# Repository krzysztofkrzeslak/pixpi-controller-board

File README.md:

### PiXPi controller board source

This are sources for PiXPi controller board

Morea bout project on: https://hackaday.io/project/166730-pixpi-dslr-camera-controller

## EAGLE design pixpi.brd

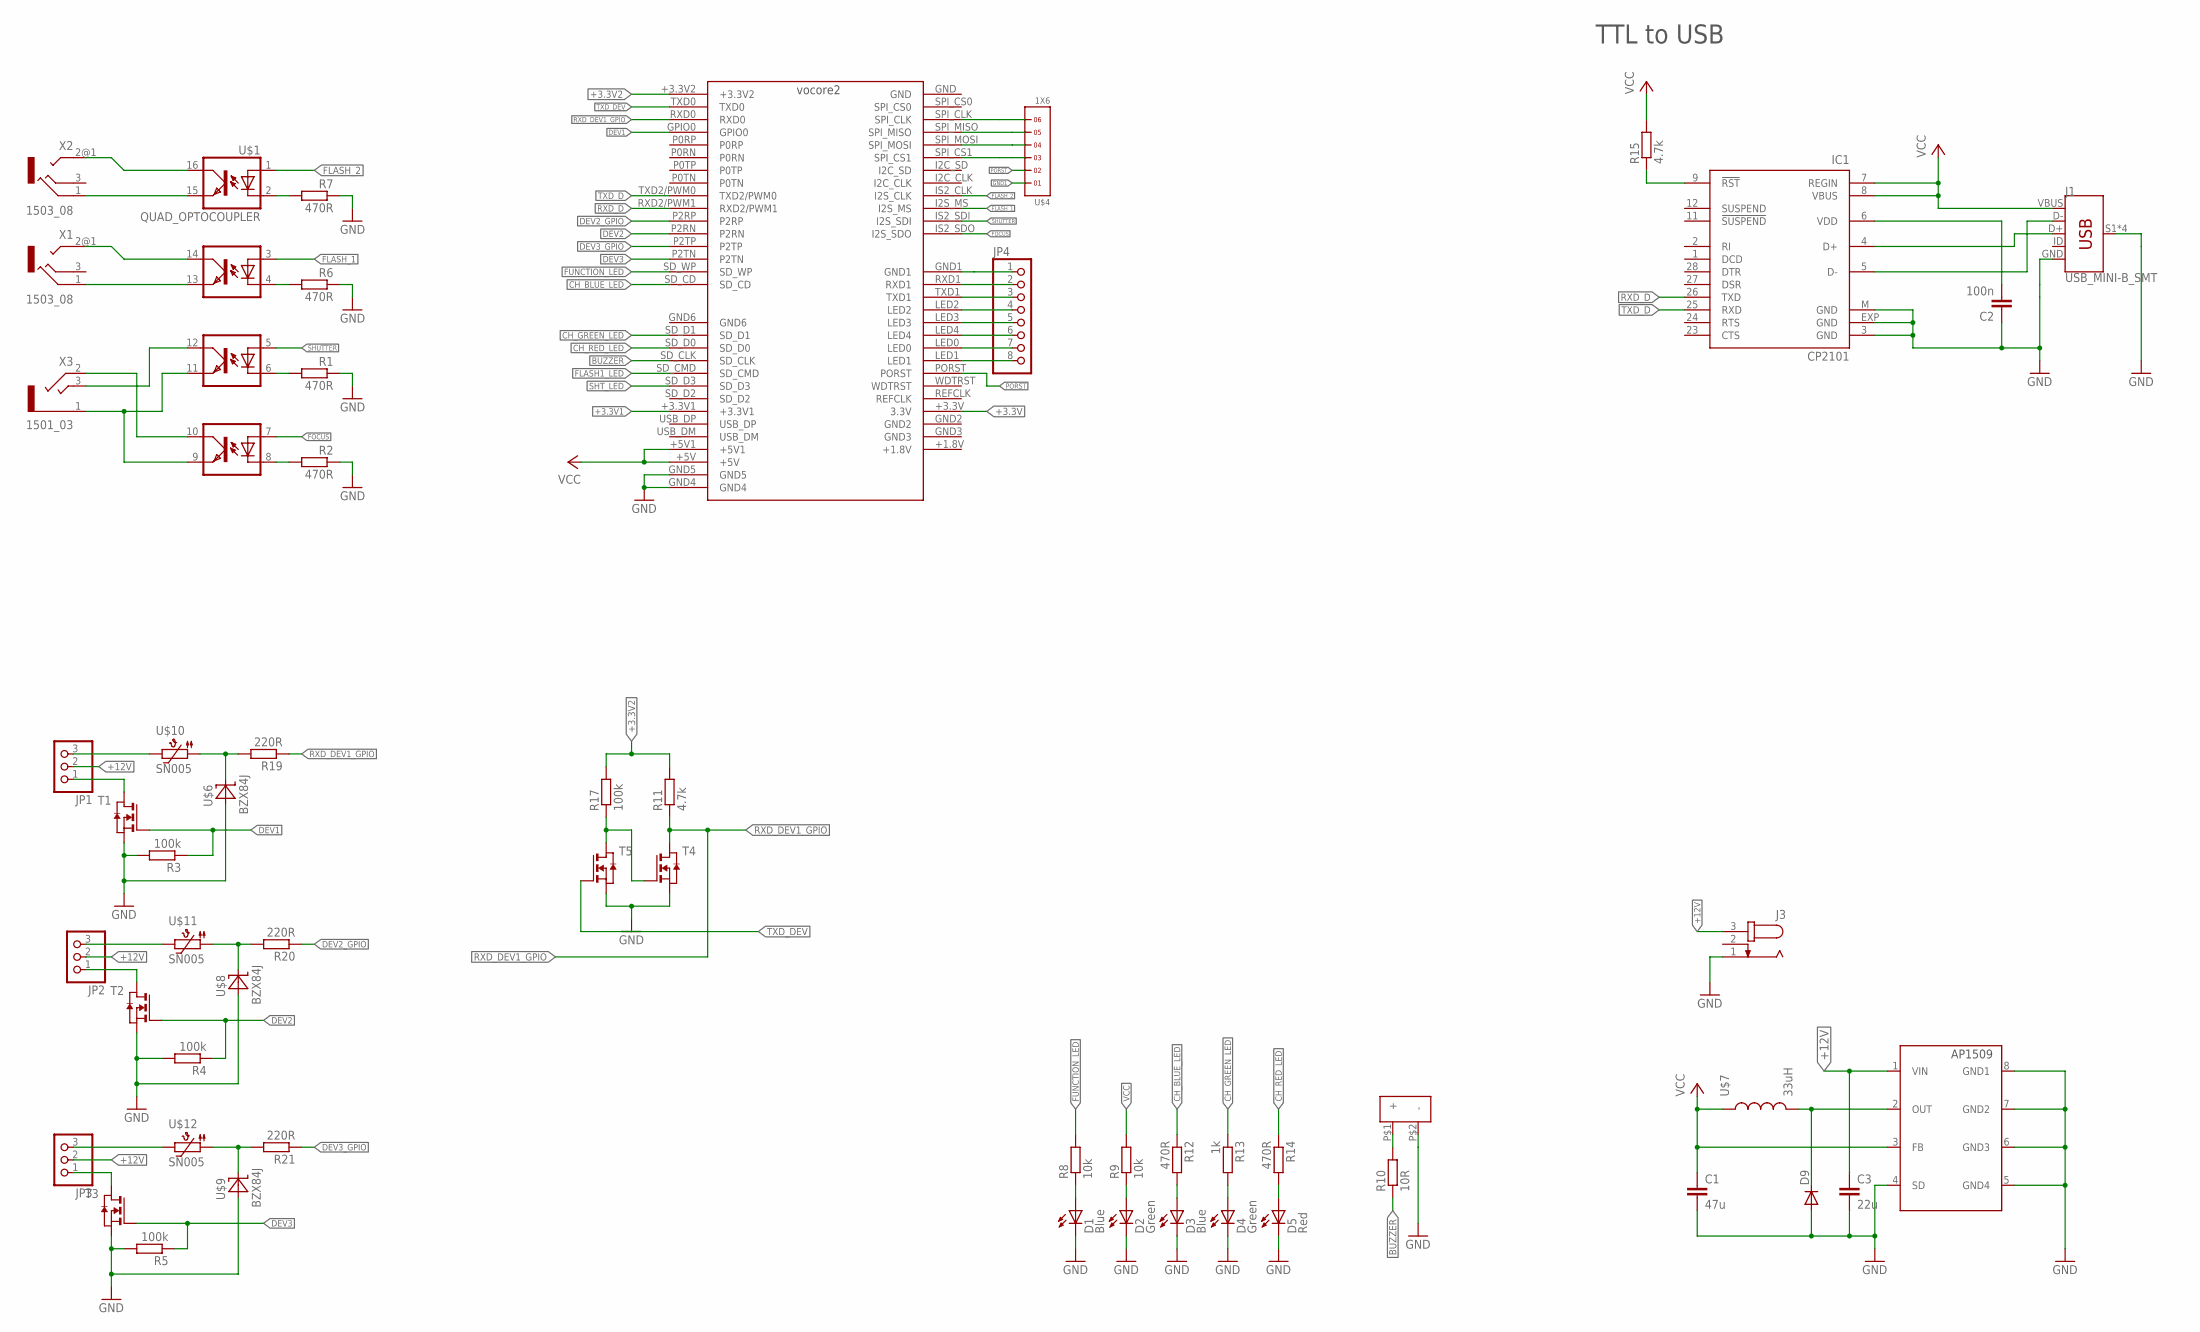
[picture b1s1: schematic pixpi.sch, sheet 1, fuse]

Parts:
C1: 47u; C1210
C2: 100n; C0805
C3: 22u; C1210
D1: Blue; CHIPLED_0603
D2: Green; CHIPLED_0603
D3: Blue; CHIPLED_1206
D4: Green; CHIPLED_1206
D5: Red; CHIPLED_1206
D9: DIODE-SOD323-W; SOD323-W
IC1: CP2101; MLP28
J1: USB_MINI-B_SMT; USB-MINIB
J3: JACK-PLUG0; SPC4077
JP1, JP2, JP3: PINHD-1X3/90; 1X03/90
JP4: PINHD-1X8; 1X08
R1, R2, R6, R7, R12, R14: 470R; R0805
R3, R4, R5, R17: 100k; R0805
R8, R9: 10k; R0805
R10: 10R; R0805
R11, R15: 4.7k; R0805
R13: 1k; R0805
R19, R20, R21: 220R; R0805
T1, T2, T3, T4, T5: NMOSSOT23; SOT-23
U$1: QUAD_OPTOCOUPLER; SO16
U$2: VOCORE2
U$3: LD-BZEG-0905
U$4: 1X6
U$5: AP1509; SOP08
U$6, U$8, U$9: BZX84J; SOD323_ST
U$7: 33uH; DJNR6028
U$10, U$11, U$12: SN005; R1206
X1, X2: 1503_08
X3: 1501_03

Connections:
+3.3V: U$2.+3.3V (3.3V)
+3.3V1: U$2.+3.3V1
+3.3V2: R11.2, R17.2, U$2.+3.3V2
+12V: C3.1, J3.3, JP1.2, JP2.2, JP3.2, U$5.1 (VIN)
BUZZER: R10.1, U$2.SD_CLK
CH_BLUE_LED: R12.1, U$2.SD_CD
CH_GREEN_LED: R13.1, U$2.SD_D1
CH_RED_LED: R14.1, U$2.SD_D0
DEV1: R3.1, T1.3 (G), U$2.GPIO0
DEV2: R4.1, T2.3 (G), U$2.P2RN
DEV2_GPIO: R20.1, U$2.P2RP
DEV3: R5.1, T3.3 (G), U$2.P2TN
DEV3_GPIO: R21.1, U$2.P2TP
FLASH1_LED: U$2.SD_CMD
FLASH_1: U$1.3 (A1), U$2.I2S_MS
FLASH_2: U$1.1 (A), U$2.IS2_CLK (I2S_CLK)
FOCUS: U$1.7 (A3), U$2.IS2_SDO (I2S_SDO)
FUNCTION_LED: R8.2, U$2.SD_WP
GND: C1.2, C2.1, C3.2, D1.C, D2.C, D3.C, D4.C, D5.C, D9.A, IC1.3 (GND), IC1.EXP (GND), IC1.M (GND), J1.GND, J1.S1 (SHIELD), J1.S2 (SHIELD), J1.S3 (SHIELD), J1.S4 (SHIELD), J3.1, R1.1, R2.1, R3.2, R4.2, R5.2, R6.1, R7.1, T1.2 (S), T2.2 (S), T3.2 (S), T4.2 (S), T5.2 (S), U$2.GND4, U$2.GND5, U$3.P$2 (-), U$5.4 (SD), U$5.5 (GND4), U$5.6 (GND3), U$5.7 (GND2), U$5.8 (GND1), U$6.A, U$8.A, U$9.A
GND1: JP4.1, U$2.GND1, U$4.1
unnamed: JP2.1, T2.1 (D)
unnamed: R19.2, U$6.C, U$10.1
unnamed: D9.C, U$5.2 (OUT), U$7.P$4 (2)
unnamed: U$1.13 (EMIT1), X1.1
unnamed: U$1.10 (COL3), X3.2
unnamed: JP1.3, U$10.2
unnamed: R6.2, U$1.4 (C1)
unnamed: JP3.1, T3.1 (D)
unnamed: R21.2, U$9.C, U$12.1
unnamed: U$1.12 (COL2), X3.3
unnamed: U$1.9 (EMIT3), U$1.11 (EMIT2), X3.1
unnamed: R1.2, U$1.6 (C2)
unnamed: R10.2, U$3.P$1 (+)
unnamed: R2.2, U$1.8 (C3)
unnamed: JP2.3, U$11.2
unnamed: U$1.14 (COL1), X1.2@1 (2)
unnamed: JP3.3, U$12.2
unnamed: D2.A, R9.1
unnamed: D1.A, R8.1
unnamed: R20.2, U$8.C, U$11.1
unnamed: JP1.1, T1.1 (D)
unnamed: IC1.9 (!RST), R15.1
unnamed: U$2.SPI_CS1, U$4.3
unnamed: IC1.5 (D-), J1.D-
unnamed: IC1.4 (D+), J1.D+
unnamed: C2.2, IC1.6 (VDD)
unnamed: U$2.SPI_MOSI, U$4.4
unnamed: U$2.SPI_MISO, U$4.5
unnamed: U$2.SPI_CLK, U$4.6
unnamed: R17.1, T4.3 (G), T5.1 (D)
unnamed: D3.A, R12.2
unnamed: D4.A, R13.2
unnamed: U$1.15 (EMIT), X2.1
unnamed: U$1.16 (COL), X2.2@1 (2)
unnamed: D5.A, R14.2
unnamed: R7.2, U$1.2 (C)
unnamed: JP4.2, U$2.RXD1
unnamed: JP4.3, U$2.TXD1
unnamed: JP4.4, U$2.LED2
unnamed: JP4.5, U$2.LED3
unnamed: JP4.6, U$2.LED4
unnamed: JP4.7, U$2.LED0
unnamed: JP4.8, U$2.LED1
PORST: U$2.PORST, U$4.2
RXD_D: IC1.26 (TXD), U$2.RXD2/PWM1
RXD_DEV1_GPIO: R11.1, R19.1, T4.1 (D), U$2.RXD0
SHT_LED: U$2.SD_D3
SHUTTER: U$1.5 (A2), U$2.IS2_SDI (I2S_SDI)
TXD_D: IC1.25 (RXD), U$2.TXD2/PWM0
TXD_DEV: T5.3 (G), U$2.TXD0
VCC: C1.1, IC1.7 (REGIN), IC1.8 (VBUS), J1.VBUS, R9.2, R15.2, U$2.+5V, U$2.+5V1, U$5.3 (FB), U$7.P$3 (1)

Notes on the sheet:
TTL to USB

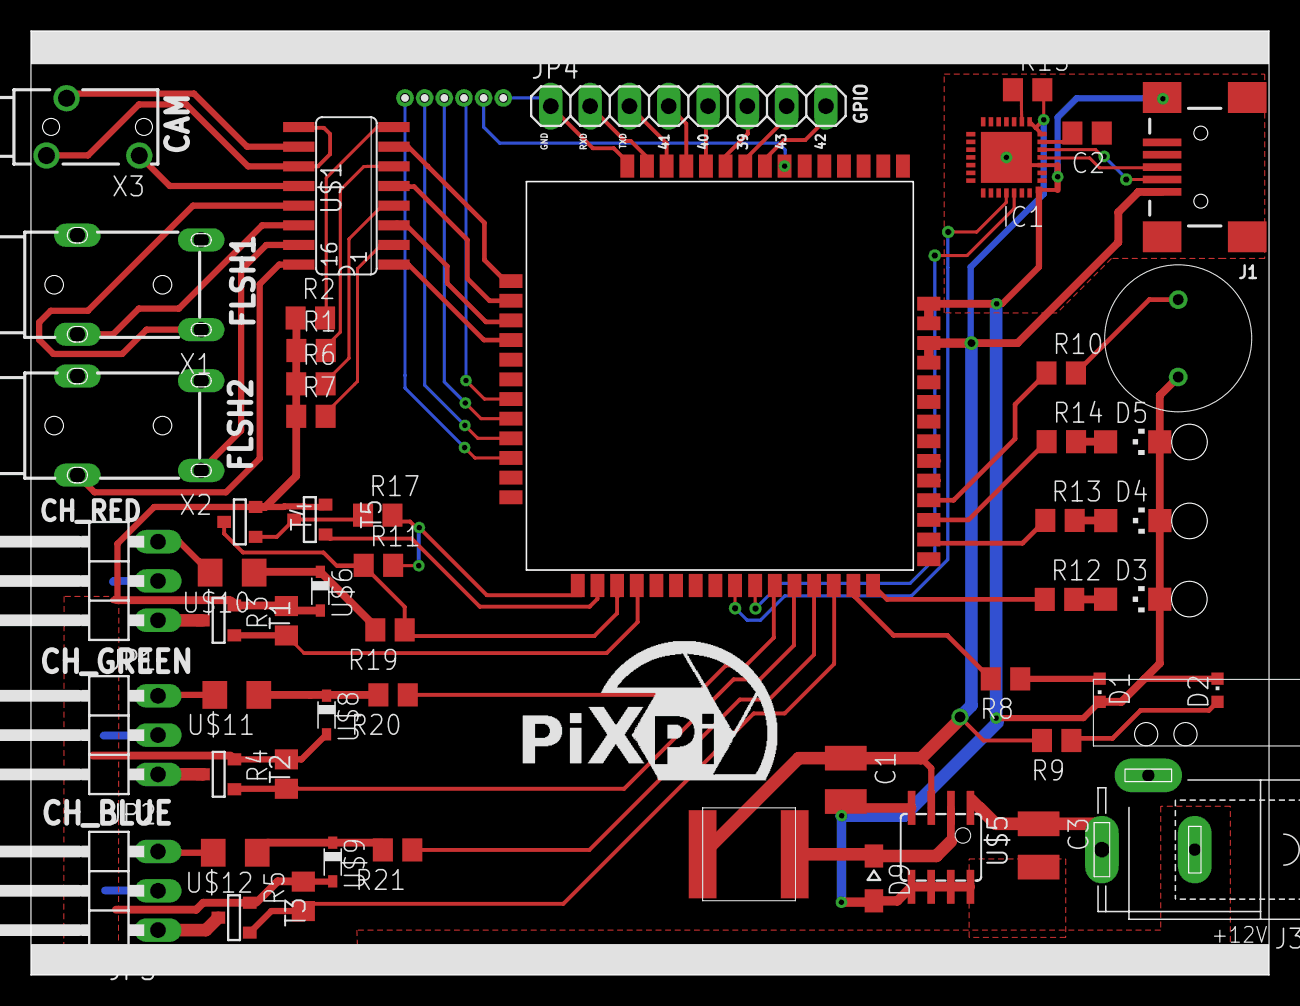
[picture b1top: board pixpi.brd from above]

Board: 2 copper layers, 79.9 x 60.9 mm, 55 parts (0 on the bottom side), 67 nets.

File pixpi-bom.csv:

Part,Value,Device,Package,Model
C1,47u,CC1210,C1210,
C2,100n,C,C0805,
C3,22u,CC1210,C1210,
D1,Blue,LEDCHIPLED_0603,CHIPLED_0603,FYLS-0603UBC 
D2,Green,LEDCHIPLED_0603,CHIPLED_0603,CL-197HG5-CF
D3,Blue,LEDCHIPLED_1206,CHIPLED_1206,FYLS-1206UBC
D4,Green,LEDCHIPLED_1206,CHIPLED_1206,FYLS-1206PGC 
D5,Red,LEDCHIPLED_1206,CHIPLED_1206,FYLS-1206URC
D9,,DIODE-SOD323-W,SOD323-W,BAS3010A03WE6327HTSA1 
IC1,CP2101,CP2101,MLP28,
J1,USB_MINI-B_SMT,USB_MINI-B_SMT,USB-MINIB,
J3,,JACK-PLUG0,SPC4077, NINIGI PC-GK2.1 
JP1,,PINHD-1X3/90,1X03/90, FCI 76382-303LF 
JP2,,PINHD-1X3/90,1X03/90, FCI 76382-303LF 
JP3,,PINHD-1X3/90,1X03/90, FCI 76382-303LF 
JP4,,PINHD-1X8,1X08,
R1,470R,R-EU_R0805,R0805,
R2,470R,R-EU_R0805,R0805,
R3,100k,R-EU_R0805,R0805,
R4,100k,R-EU_R0805,R0805,
R5,100k,R-EU_R0805,R0805,
R6,470R,R-EU_R0805,R0805,
R7,470R,R-EU_R0805,R0805,
R8,10k,R-EU_R0805,R0805,
R9,10k,R-EU_R0805,R0805,
R10,10R,R-EU_R0805,R0805,
R11,4.7k,R-EU_R0805,R0805,
R12,470R,R-EU_R0805,R0805,
R13,1k,R-EU_R0805,R0805,
R14,470R,R-EU_R0805,R0805,
R15,4.7k,R-EU_R0805,R0805,
R17,100k,R-EU_R0805,R0805,
R19,220R,R-EU_R0805,R0805,
R20,220R,R-EU_R0805,R0805,
R21,220R,R-EU_R0805,R0805,
T1,,NMOSSOT23,SOT-23,TSM2312CX
T2,,NMOSSOT23,SOT-23,TSM2312CX
T3,,NMOSSOT23,SOT-23,TSM2312CX
T4,,NMOSSOT23,SOT-23,2N7002
T5,,NMOSSOT23,SOT-23,2N7002
U$1,QUAD_OPTOCOUPLER,QUAD_OPTOCOUPLER,SO16,TCMT4100
U$2,VOCORE2,VOCORE2,VOCORE2,
U$3,LD-BZEG-0905,LD-BZEG-0905,LD-BZEG-0905,LD-BZEG-0905
U$4,1X6,1X6,1X6,
U$5,AP1509,AP1509,SOP08,
U$6,BZX84J,BZX84J,SOD323_ST,BZX84J-B3V6.115 
U$7,33uH,DJNR6028,DJNR6028,
U$8,BZX84J,BZX84J,SOD323_ST,BZX84J-B3V6.115 
U$9,BZX84J,BZX84J,SOD323_ST,BZX84J-B3V6.115 
U$10,SN005,SN005,R1206, ECE SN005-60 
U$11,SN005,SN005,R1206, ECE SN005-60 
U$12,SN005,SN005,R1206, ECE SN005-60 
X1,1503_08,1503_08,1503_08,
X2,1503_08,1503_08,1503_08, LUMBERG 1503 08 
X3,1501_03,1501_03,1501_03,1501-03

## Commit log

2019-09-29 image url tweak

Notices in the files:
parts and their libraries:
SparkFun-Connectors: Licensing: Creative Commons ShareAlike 4.0 International - https://creativecommons.org/licenses/by-sa/4.0
